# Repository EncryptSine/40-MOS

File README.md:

# 40-MOS (40-Mathyllein Ortholinear Slider)

A 40% ortholinear keyboard (4x12) with a slider potentiometer on the right side.

## Overview

- 4x12 ortholinear layout
- Slide potentiometer on the right
- Pro Micro (USB-C), sitting top-right under the slider
- Runs QMK, configurable with VIA or Vial

## Firmware

The board runs [QMK](https://qmk.fm/) and the keymap can be changed with [VIA](https://usevia.app/) or [Vial](https://get.vial.today/).

Slider support (read as an analog input) isn't in the firmware yet. I'll add it when I get the time.

## Case

Two options are included:

- Sandwich case (DXF / SVG files)
- 3D printed case (STL files). I haven't printed or tested this one yet.

## Build

1. Flash QMK onto the Pro Micro.
2. Solder the switches, diodes and the potentiometer to the PCB.
3. Put everything in the case of your choice.
4. Set up your keymap in VIA/Vial, or edit it and recompile with QMK.

## Pinout

| Row / Col | Pin |
|-----------|-----|
| Row 0     | D0  |
| Row 1     | D1  |
| Row 2     | D2  |
| Row 3     | D3  |
| Col 0     | D4  |
| Col 1     | C6  |
| Col 2     | D7  |
| Col 3     | E6  |
| Col 4     | B4  |
| Col 5     | B5  |
| Col 6     | B6  |
| Col 7     | B2  |
| Col 8     | B3  |
| Col 9     | B1  |
| Col 10    | F7  |
| Col 11    | F6  |

## Pictures

## Ideas for later

Things I might add in a future revision:

- Per-key backlight
- LEDs showing the active layer, with a different color for each layer
- Hot-swap sockets, so switches don't need soldering
- SMD parts instead of through-hole
- Underglow LEDs between the sandwich plates
- More potentiometers or some rotary encoders

## Thanks

Thanks to [MiPSR](https://github.com/MiPSR) for the inspiration, the help and everything I learned along the way :3

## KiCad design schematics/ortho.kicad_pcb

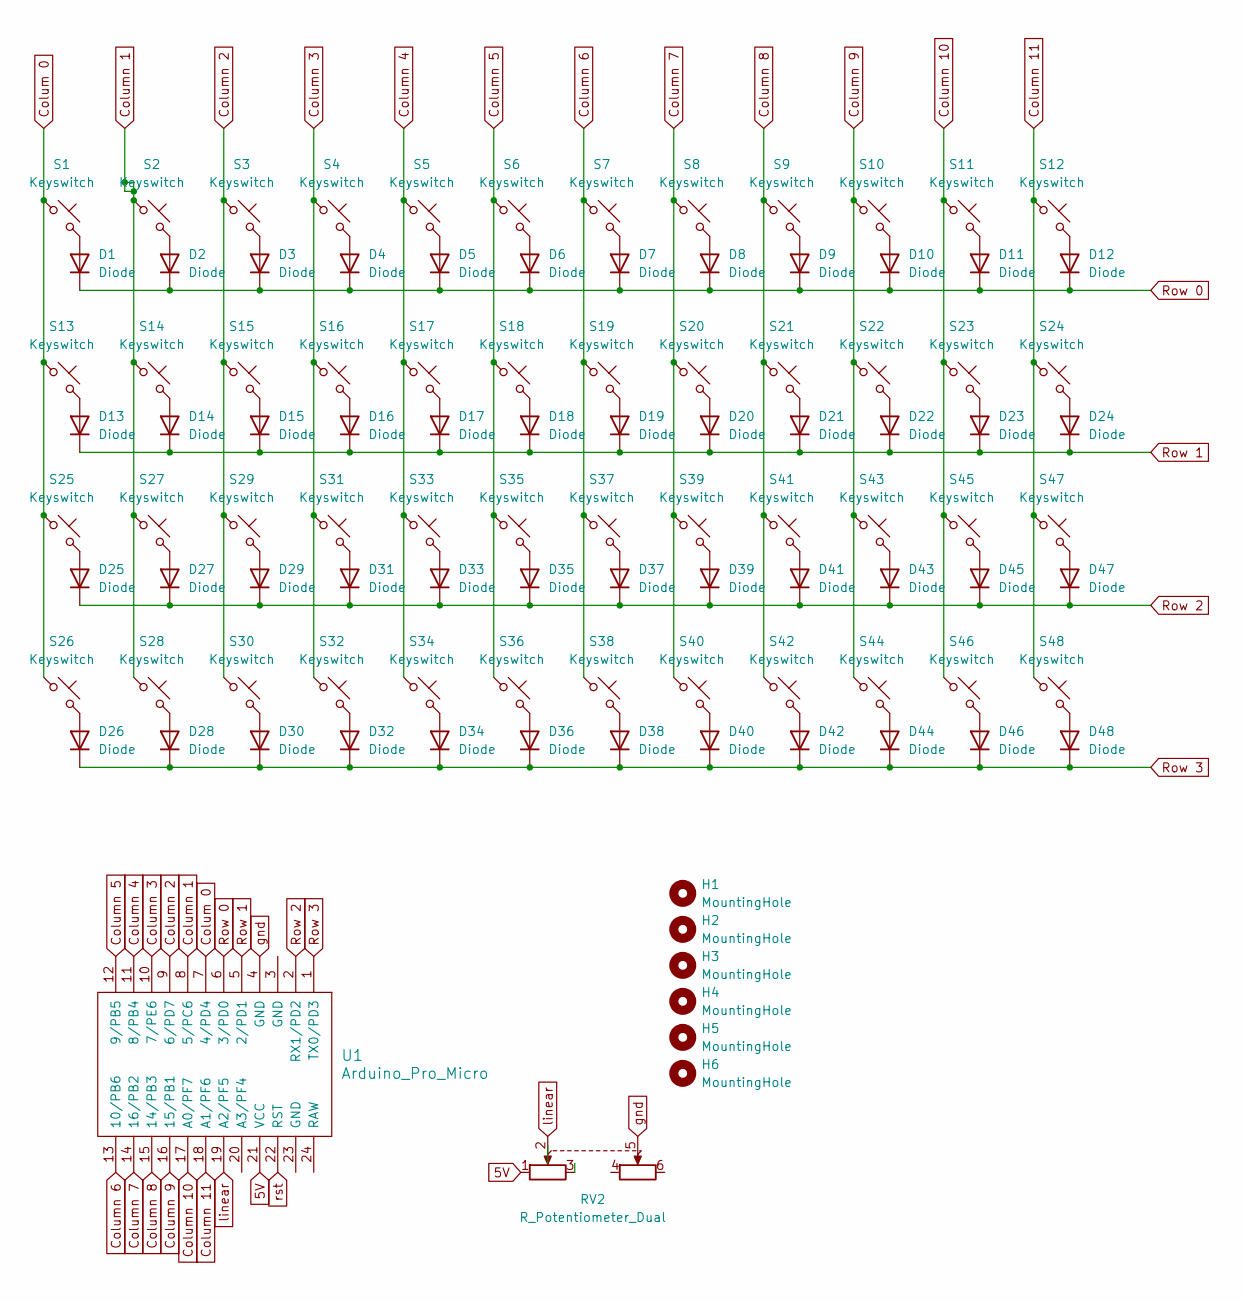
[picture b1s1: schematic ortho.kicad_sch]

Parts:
D1, D2, D3, D4, D5, D6, D7, D8, D9, D10, D11, D12, D13, D14, D15, D16, D17, D18, D19, D20, D21, D22, D23, D24, D25, D26, D27, D28, D29, D30, D31, D32, D33, D34, D35, D36, D37, D38, D39, D40, D41, D42, D43, D44, D45, D46, D47, D48: Diode; Diode_DO-35
H1, H2, H3, H4, H5, H6: MountingHole; MountingHole_2.2mm_M2
RV2: R_Potentiometer_Dual; B10K
S1, S2, S3, S4, S5, S6, S7, S8, S9, S10, S11, S12, S13, S14, S15, S16, S17, S18, S19, S20, S21, S22, S23, S24, S25, S26, S27, S28, S29, S30, S31, S32, S33, S34, S35, S36, S37, S38, S39, S40, S41, S42, S43, S44, S45, S46, S47, S48: Keyswitch; MX_PCB_1.00u
U1: Arduino_Pro_Micro

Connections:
5V: RV2.1, U1.21 (VCC)
Colum 0: S1.1, S13.1, S25.1, S26.1, U1.7 (4/PD4)
Column 1: S2.1, S14.1, S27.1, S28.1, U1.8 (5/PC6)
Column 2: S3.1, S15.1, S29.1, S30.1, U1.9 (6/PD7)
Column 3: S4.1, S16.1, S31.1, S32.1, U1.10 (7/PE6)
Column 4: S5.1, S17.1, S33.1, S34.1, U1.11 (8/PB4)
Column 5: S6.1, S18.1, S35.1, S36.1, U1.12 (9/PB5)
Column 6: S7.1, S19.1, S37.1, S38.1, U1.13 (10/PB6)
Column 7: S8.1, S20.1, S39.1, S40.1, U1.14 (16/PB2)
Column 8: S9.1, S21.1, S41.1, S42.1, U1.15 (14/PB3)
Column 9: S10.1, S22.1, S43.1, S44.1, U1.16 (15/PB1)
Column 10: S11.1, S23.1, S45.1, S46.1, U1.17 (A0/PF7)
Column 11: S12.1, S24.1, S47.1, S48.1, U1.18 (A1/PF6)
unnamed: D1.2 (A), S1.2
unnamed: D2.2 (A), S2.2
unnamed: D3.2 (A), S3.2
unnamed: D4.2 (A), S4.2
unnamed: D5.2 (A), S5.2
unnamed: D6.2 (A), S6.2
unnamed: D7.2 (A), S7.2
unnamed: D8.2 (A), S8.2
unnamed: D9.2 (A), S9.2
unnamed: D10.2 (A), S10.2
unnamed: D11.2 (A), S11.2
unnamed: D12.2 (A), S12.2
unnamed: D13.2 (A), S13.2
unnamed: D14.2 (A), S14.2
unnamed: D15.2 (A), S15.2
unnamed: D16.2 (A), S16.2
unnamed: D17.2 (A), S17.2
unnamed: D18.2 (A), S18.2
unnamed: D19.2 (A), S19.2
unnamed: D20.2 (A), S20.2
unnamed: D21.2 (A), S21.2
unnamed: D22.2 (A), S22.2
unnamed: D23.2 (A), S23.2
unnamed: D24.2 (A), S24.2
unnamed: D25.2 (A), S25.2
unnamed: D26.2 (A), S26.2
unnamed: D27.2 (A), S27.2
unnamed: D28.2 (A), S28.2
unnamed: D29.2 (A), S29.2
unnamed: D30.2 (A), S30.2
unnamed: D31.2 (A), S31.2
unnamed: D32.2 (A), S32.2
unnamed: D33.2 (A), S33.2
unnamed: D34.2 (A), S34.2
unnamed: D35.2 (A), S35.2
unnamed: D36.2 (A), S36.2
unnamed: D37.2 (A), S37.2
unnamed: D38.2 (A), S38.2
unnamed: D39.2 (A), S39.2
unnamed: D40.2 (A), S40.2
unnamed: D41.2 (A), S41.2
unnamed: D42.2 (A), S42.2
unnamed: D43.2 (A), S43.2
unnamed: D44.2 (A), S44.2
unnamed: D45.2 (A), S45.2
unnamed: D46.2 (A), S46.2
unnamed: D47.2 (A), S47.2
unnamed: D48.2 (A), S48.2
Row 0: D1.1 (K), D2.1 (K), D3.1 (K), D4.1 (K), D5.1 (K), D6.1 (K), D7.1 (K), D8.1 (K), D9.1 (K), D10.1 (K), D11.1 (K), D12.1 (K), U1.6 (3/PD0)
Row 1: D13.1 (K), D14.1 (K), D15.1 (K), D16.1 (K), D17.1 (K), D18.1 (K), D19.1 (K), D20.1 (K), D21.1 (K), D22.1 (K), D23.1 (K), D24.1 (K), U1.5 (2/PD1)
Row 2: D25.1 (K), D27.1 (K), D29.1 (K), D31.1 (K), D33.1 (K), D35.1 (K), D37.1 (K), D39.1 (K), D41.1 (K), D43.1 (K), D45.1 (K), D47.1 (K), U1.2 (RX1/PD2)
Row 3: D26.1 (K), D28.1 (K), D30.1 (K), D32.1 (K), D34.1 (K), D36.1 (K), D38.1 (K), D40.1 (K), D42.1 (K), D44.1 (K), D46.1 (K), D48.1 (K), U1.1 (TX0/PD3)
gnd: RV2.5, U1.4 (GND)
linear: RV2.2, U1.19 (A2/PF5)
rst: U1.22 (RST)

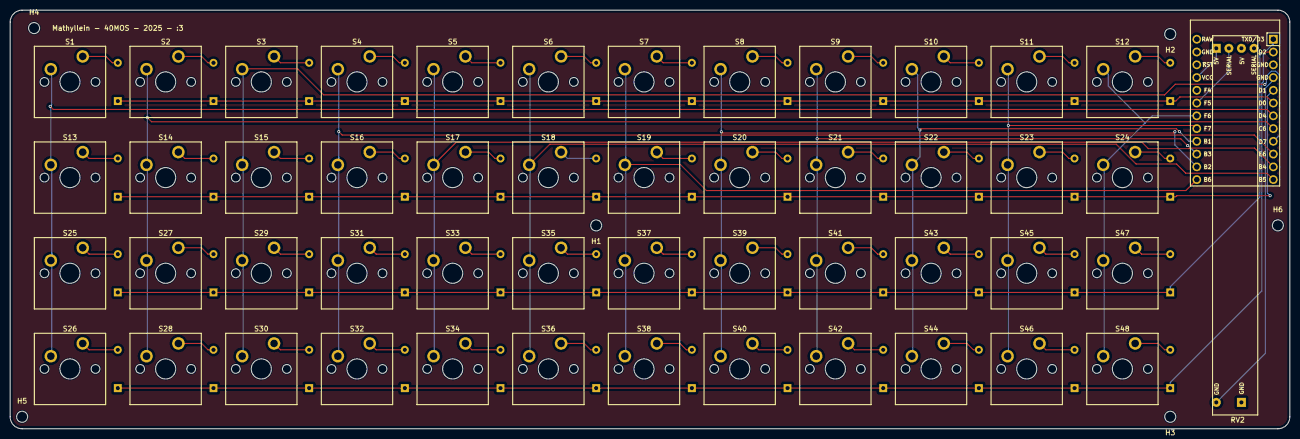
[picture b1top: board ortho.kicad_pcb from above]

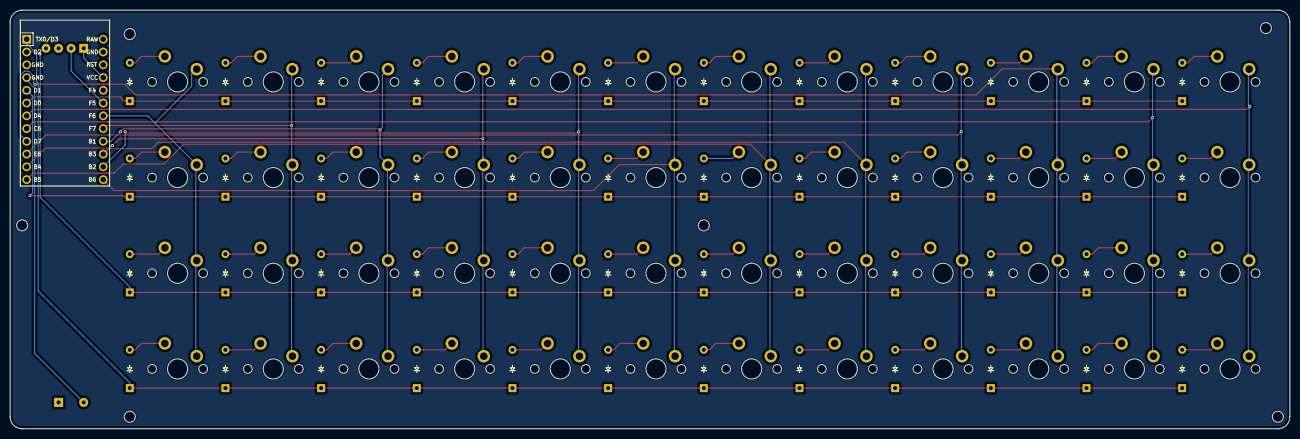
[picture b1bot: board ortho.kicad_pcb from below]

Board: 2 copper layers, 254.8 x 83.3 mm, 104 parts (49 on the bottom side), 67 nets.

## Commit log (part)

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2025-08-23 all except images
2025-08-23 add all
2025-08-23 readme
